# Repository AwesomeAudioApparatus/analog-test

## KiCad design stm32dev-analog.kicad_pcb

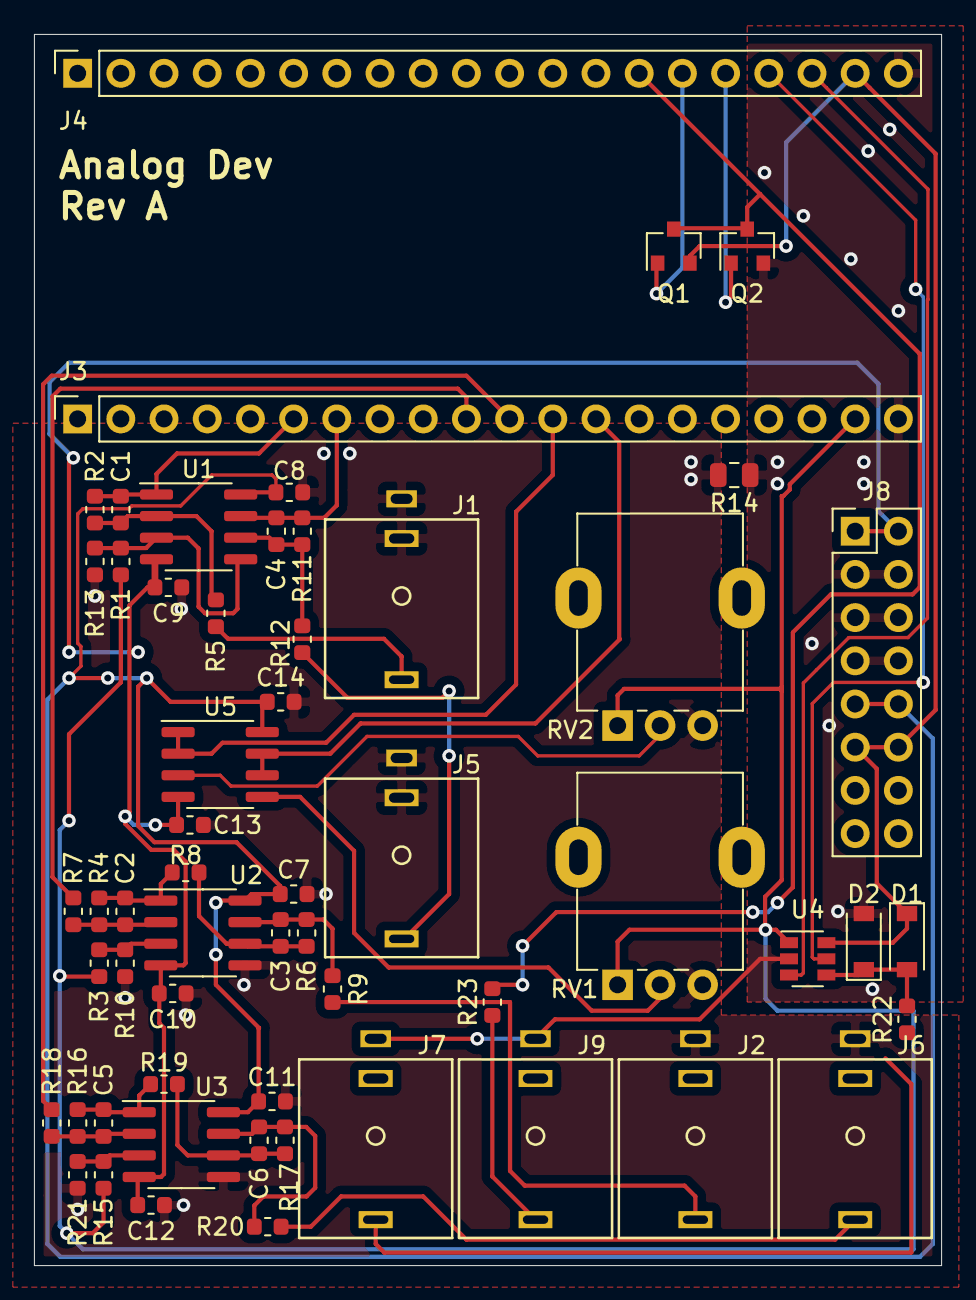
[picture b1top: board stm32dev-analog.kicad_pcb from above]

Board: 2 copper layers, 53.3 x 72.4 mm, 57 parts (0 on the bottom side), 39 nets.

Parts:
C1, C4: 2.2nF; C_0603_1608Metric
C2: 20pF; C_0603_1608Metric
C3, C6: 1nF; C_0603_1608Metric
C5: 200pF; C_0603_1608Metric
C7, C8, C9, C10, C11, C12, C13, C14: 0.1uF; C_0603_1608Metric
D1, D2: B5819W; D_SOD-123
J1, J2, J5, J6, J7, J9: PJ301M-12
J3, J4: Conn_01x20_Male; PinSocket_1x20_P2.54mm_Vertical
J8: Conn_02x08_Odd_Even; PinHeader_2x08_P2.54mm_Vertical
Q1: LBSS84LT1G; SOT-23
Q2: 2N7002; SOT-23
R1: 18k; R_0603_1608Metric
R2, R11: 3k3; R_0603_1608Metric
R3, R15: 36k; R_0603_1608Metric
R4: 330k; R_0603_1608Metric
R5, R6, R12, R17: 20k; R_0603_1608Metric
R7: 100k; R_0603_1608Metric
R8, R18, R19: 10k; R_0603_1608Metric
R9, R20: 100; R_0603_1608Metric
R10, R21: 22k; R_0603_1608Metric
R13: 13k; R_0603_1608Metric
R14: 0R; R_0805_2012Metric
R16: 33k; R_0603_1608Metric
R22, R23: 1k; R_0603_1608Metric
RV1, RV2: Potentiometer_Alpha_RD901F-40-00D_Single_Vertical
U1, U2, U3, U5: TL072; SOIC-8_3.9x4.9mm_P1.27mm
U4: 74LVC1T45W6; SOT-23-6

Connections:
+3V3: J3.19, R1.2, R3.1, R15.1, RV1.1, RV2.1, U4.1
+5V: D1.1, J4.19, J8.11, J8.12, Q1.2, U4.6
+12V: C7.1, C8.1, C11.1, C14.1, J8.9, J8.10, U1.8, U2.8, U3.8, U5.8
-12V: C9.1, C10.1, C12.1, C13.1, J8.1, J8.2, U1.4, U2.4, U3.4, U5.4
GNDA: C7.2, C8.2, C9.2, C10.2, C11.2, C12.2, C13.2, C14.2, J1.S, J1.TN, J2.S, J5.S, J5.TN, J6.S, R10.2, R13.1, R14.2, R21.2, RV1.3, RV2.3, U2.5, U3.5
GNDD: D2.2, J3.20, J4.20, J7.S, J8.3, J8.4, J8.5, J8.6, J8.7, J8.8, J9.S, Q2.2, R14.1, U4.2
unnamed: C1.1, R2.2, R5.1, U1.2
unnamed: C2.1, R4.2, R7.1, U2.2
unnamed: C2.2, R4.1, R8.2, U2.1
unnamed: C3.1, R6.2, R8.1, U2.6
unnamed: C3.2, R6.1, R9.2, U2.7
unnamed: C4.1, R11.2, R12.1, U1.6
unnamed: C5.1, R16.2, R18.1, U3.2
unnamed: C5.2, R16.1, R19.2, U3.1
unnamed: C6.1, R17.2, R19.1, U3.6
unnamed: C6.2, R17.1, R20.2, U3.7
unnamed: D1.2, D2.1, R22.2, U4.4
unnamed: J1.T, R5.2
unnamed: J2.T, R9.1
unnamed: J5.T, R12.2
unnamed: J6.T, R20.1
unnamed: J7.T, R22.1
unnamed: J9.T, R23.1
unnamed: R1.1, R13.2, U1.3, U1.5
unnamed: R3.2, R10.1, U2.3
unnamed: R15.2, R21.1, U3.3
unnamed: RV1.2, U5.5
unnamed: RV2.2, U5.3
PA0: C1.2, J3.6, R2.1, U1.1
PA1: C4.2, J3.7, R11.1, U1.7
PA4: J3.10, R7.2
PA5: J3.11, R18.2
PA6: J3.12, U5.1, U5.2
PA7: J3.13, U5.6, U5.7
PB10: J4.18, U4.3
PB11: J4.17, U4.5
PB12: J4.16, Q2.1
PB13: J4.15, Q1.1
PB14: J4.14, Q1.3, Q2.3, R23.2

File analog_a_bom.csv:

Comment,Designator,Footprint,LCSC
"20pF","C2","Capacitor_SMD:C_0603_1608Metric","C1648"
"1nF","C3,C6","Capacitor_SMD:C_0603_1608Metric","C1588"
"2.2nF","C4,C1","Capacitor_SMD:C_0603_1608Metric","C1604"
"200pF","C5","Capacitor_SMD:C_0603_1608Metric","C1600"
"0.1uF","C7,C10,C8,C9,C14,C11,C12,C13","Capacitor_SMD:C_0603_1608Metric","C14663"
"B5819W","D1,D2","Diode_SMD:D_SOD-123","C8598"
"Conn_01x20_Male","J4,J3","Connector_PinSocket_2.54mm:PinSocket_1x20_P2.54mm_Vertical"
"~","J5,J1,J2,J7,J6,J9","aaa:PJ301M-12"
"Conn_02x08_Odd_Even","J8","Connector_PinHeader_2.54mm:PinHeader_2x08_P2.54mm_Vertical"
"LBSS84LT1G","Q1","Package_TO_SOT_SMD:SOT-23","C8492"
"2N7002","Q2","Package_TO_SOT_SMD:SOT-23","C8545"
"18k","R1","Resistor_SMD:R_0603_1608Metric","C25810"
"22k","R10,R21","Resistor_SMD:R_0603_1608Metric","C31850"
"13k","R13","Resistor_SMD:R_0603_1608Metric","C22797"
"0R","R14","Resistor_SMD:R_0805_2012Metric","C17477"
"33k","R16","Resistor_SMD:R_0603_1608Metric","C4216"
"3k3","R2,R11","Resistor_SMD:R_0603_1608Metric","C22978"
"1k","R22,R23","Resistor_SMD:R_0603_1608Metric","C21190"
"36k","R3,R15","Resistor_SMD:R_0603_1608Metric","C23147"
"330k","R4","Resistor_SMD:R_0603_1608Metric","C23137"
"20k","R5,R12,R6,R17","Resistor_SMD:R_0603_1608Metric","C4184"
"100k","R7","Resistor_SMD:R_0603_1608Metric","C25803"
"10k","R8,R18,R19","Resistor_SMD:R_0603_1608Metric","C25804"
"100","R9,R20","Resistor_SMD:R_0603_1608Metric","C22775"
"~","RV2,RV1","aaa:Potentiometer_Alpha_RD901F-40-00D_Single_Vertical"
"TL072","U1,U2,U3,U5","Package_SO:SOIC-8_3.9x4.9mm_P1.27mm","C6961"
"74LVC1T45W6","U4","Package_TO_SOT_SMD:SOT-23-6","C168856"

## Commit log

2020-08-05 Analog board for the stm32dev to test analog performance and software platform.
2020-08-05 Fixed supply to TL072 of pots.
2020-08-05 Changed to 20pF and 200pF resp to use Basic instead of Extended part.
2020-08-05 Added fab files
2020-08-05 Fixed production files
2020-08-05 Changed BAT54 to discrete diodes to use Basic instead of Extended part.
